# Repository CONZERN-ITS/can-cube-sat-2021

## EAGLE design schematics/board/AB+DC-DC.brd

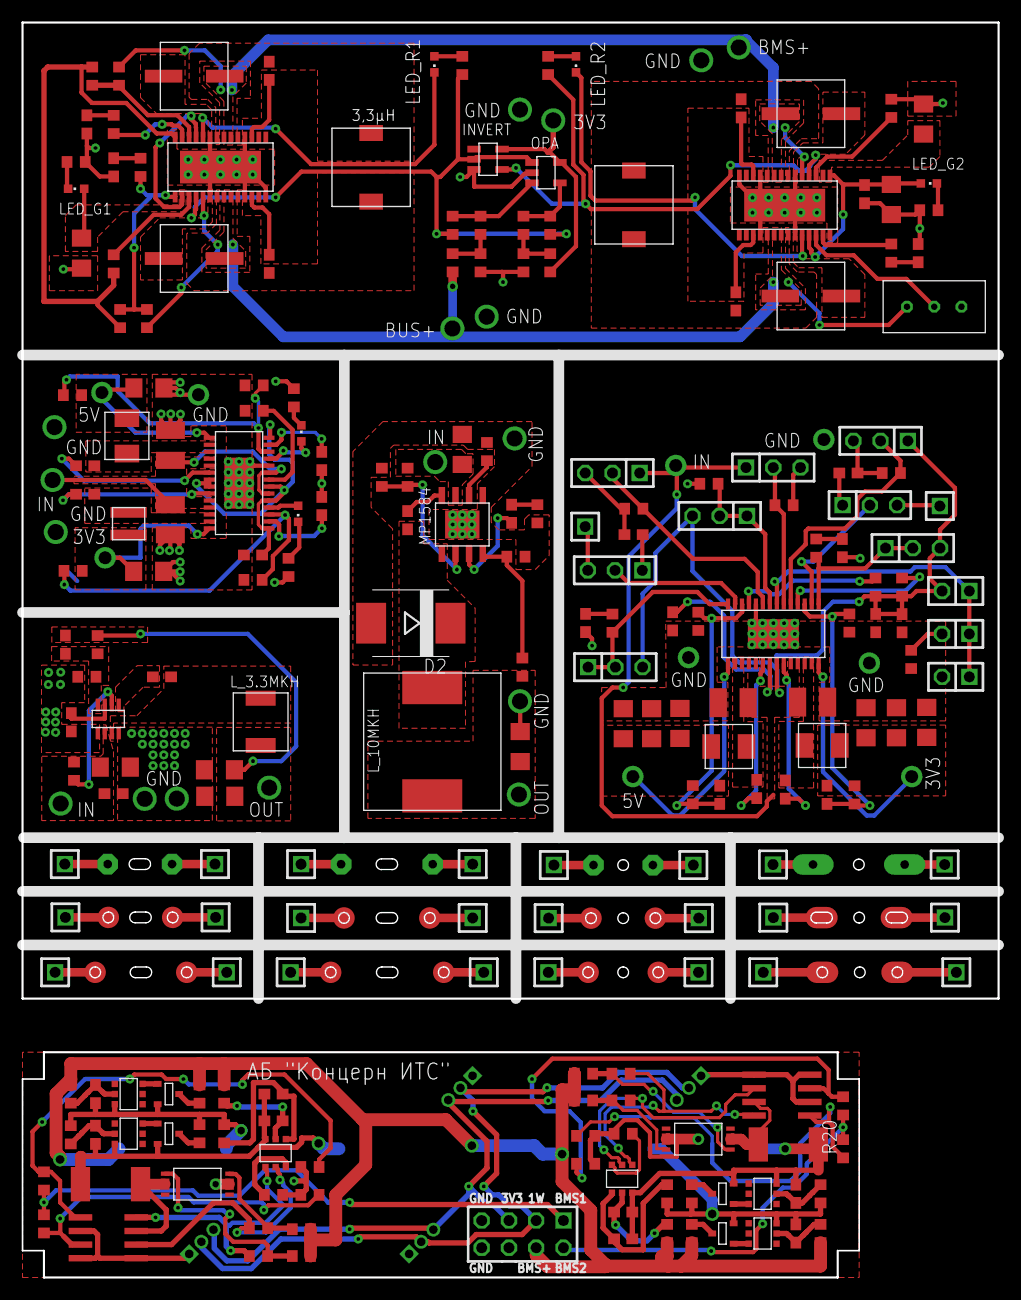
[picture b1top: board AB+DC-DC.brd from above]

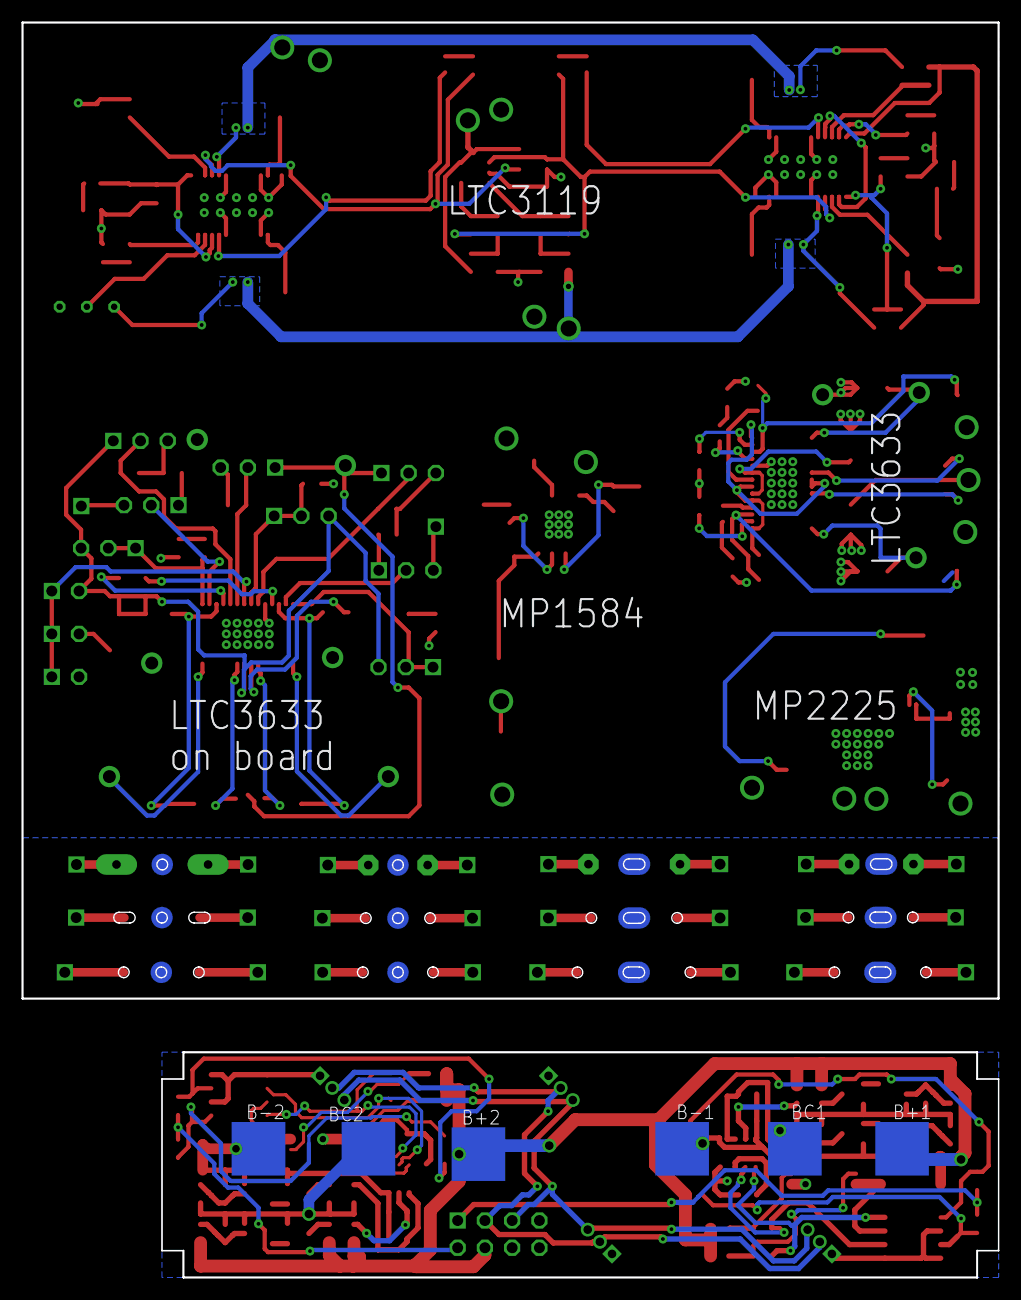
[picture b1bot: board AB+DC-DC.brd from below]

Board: 2 copper layers, 91.0 x 117.0 mm, 242 parts (6 on the bottom side), 164 nets.

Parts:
3,3µH: 3,3µ; B82472G6
3,3µH1: 3,3µH; B82472G6
AB1: 2X04
B+1, B+2: BATTERY
B-1, B-2: BATTERY
BC1, BC2: BATTERY
C1, C2, C3, C4, C5, C6, C8, C11, C12, C18, C25, C26, C27, C28, C33, C34, C48, C49, C55, C56, C61: 0,1µ; C0603
C7, C9, C13, C15, C20, C21, C38, C39, C40, C41: 22µ; C1206
C10, C42, C43, C62: 10µ; C1206
C14: 2,2µ; C0603
C16, C17, C46, C47: 47µ; C1210
C19: 33p; C0603
C22, C23, C36: 220p; C0603
C24, C30, C31: 1µ; C0603
C29, C32, C44, C45: 4.7nF; C0603
C35, C37: 10p; C0603
C50, C57: 680p; C0603
C51, C58: 4.7µ; C1206
C52: 3,3n; C0603
C53, C59: 150µ; ECAP150
C54, C60: 220µ; ECAP220
D2: SMC
DS18B20, DS18B20A, DS18B20B, DS18B20C: CONNECT1X3
INVERT: INVERTER; SOT23-5
JP1, JP2, JP3: 1X02
JP4, JP5, JP6, JP7, JP8, JP9, JP10, JP11: 1X03
JP12, JP13, JP14, JP15, JP16, JP17, JP18, JP19, JP20, JP21, JP22, JP23, JP24, JP25, JP26, JP27, JP28, JP29, JP30, JP31, JP32, JP33, JP34, JP35, JP36, JP37: 1X01
LED1, LED2: CHIPLED_0603
LED_G1, LED_G2: CHIPLED_0603
LED_R1, LED_R2: CHIPLED_0603
OPA: OPA333; SOT23-5
R1, R26, R31, R49, R60, R61, R62, R100: 2k; R0603
R2, R3, R50, R51: 330R; R0603
R4, R5, R6, R7, R9, R10, R15, R16, R52, R53, R54, R55: 100R; R0603
R8, R56: R05; R2512
R11, R12, R17, R18, R30, R34, R42, R43: 100k; R0603
R13, R14, R19, R20: 2k26; R0603
R21: 73,2k; R0603
R22: 45,3k; R0603
R23, R24, R37, R66, R74, R76: 10k; R0603
R25: 162k; R0603
R27, R94, R95, R98, R99: 200k; R0603
R28, R36: 40k2; R0603
R29: 124k; R0603
R32: 24k9; R0603
R33: 68k1; R0603
R35: 8k87; R0603
R38, R40: 13k; R0603
R39: 324k; R0603
R41, R44, R45, R65: 1M; R0603
R46: 11k5; R0603
R47: 18k7; R0603
R48, R57: 84k5; R0603
R58, R59, R67, R68, R69, R75, R77: 150k; R0603
R63: 910k; R0603
R64: 330k; R0603
R70: 24k3; R0603
R71, R73: 51k; R0603
R72: 232k; R0603
U$1, U$26: FS8205A-
U$2, U$10: MOCD217M; SOIC8
U$3, U$45: HY2120; SOT23-6
U$4, U$5, U$46, U$47: HY2213"; SOT23-6
U$6, U$7, U$48, U$49: SI2302CDS; SOT23-3
U$8, U$16: LTC3633+VIA
U$9: MP1584+VIA
U$11: 1µH; VLS3012HBX
U$12: SPM4020
U$13: L_10MKH; L_12X12
U$14: MP2225; TSOT23-8
U$15: L_3.3MKH; L_SPM5020
U$17, U$18: L_2.2MKH; L_SPM4020
U$19: GRAFITGRAFIT1; GRAFIT1
U$20: GRAFITGRAFIT1_1; GRAFIT1_1
U$21: GRAFITGRAFIT1_2; GRAFIT1_2
U$22: GRAFITGRAFIT2; GRAFIT2
U$23: GRAFITGRAFIT2_1; GRAFIT2_1
U$24: GRAFITGRAFIT2_2; GRAFIT2_2
U$25: GRAFITGRAFIT3; GRAFIT3
U$27: GRAFITGRAFIT3_1; GRAFIT3_1
U$28: GRAFITGRAFIT3_2; GRAFIT3_2
U$29: GRAFITGRAFIT4; GRAFIT4
U$30: GRAFITGRAFIT4_1; GRAFIT4_1
U$31: GRAFITGRAFIT4_2; GRAFIT4_2
U$32, U$59: LTC31191; LTC3119+VIA
U$33: 32961; 3296W

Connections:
1.65: R71.2, R73.1, R74.2
1W: AB1.3, DS18B20.2, DS18B20A.2, DS18B20B.2, DS18B20C.2
3.3: INVERT.P$5, OPA.P$5, R73.2
3V1: C9.1, R29.1, U$13.P$1
3V3: AB1.5, DS18B20.3, DS18B20A.3, DS18B20B.3, DS18B20C.3
5V: C15.1, R21.2, U$8.15, U$12.P$2
90: R65.1, R66.2, R67.2, U$59.15
A: INVERT.P$2, OPA.P$1, R61.1, R75.2, R77.2, U$59.18
B-1: B-1.P$1, C1.2, C2.2, C4.2, R8.2, U$3.6, U$5.3, U$7.2
B-2: B-2.P$1, C25.2, C26.2, C28.2, R56.2, U$45.6, U$47.3, U$49.2
BC1: BC1.P$1, C3.2, R3.2, R5.2, R7.2, U$4.3, U$6.2
BC2: BC2.P$1, C27.2, R51.2, R53.2, R55.2, U$46.3, U$48.2
BMS1: AB1.1, R13.2, R14.2
BMS2: AB1.2, R19.2, R20.2
BMS+: AB1.4, B+1.P$1, B+2.P$1, R2.2, R4.2, R6.2, R11.1, R12.2, R17.1, R18.2, R50.2, R52.2, R54.2
BUS+: C16.1, C17.1, U$8.6, U$8.9, U$8.18, U$8.19, U$8.24, U$8.25
FB1: C37.1, R47.1, R57.2, U$16.3
FB2: C35.1, R46.1, R48.2, U$16.12
GND: AB1.7, AB1.8, DS18B20.1, DS18B20A.1, DS18B20B.1, DS18B20C.1, R1.1, R49.1, R94.1, R95.1, R98.1, R99.1, U$1.23, U$2.2, U$2.4, U$2.5, U$10.2, U$10.4, U$10.5, U$26.23
GND1: C7.2, C9.2, C10.1, C12.1, C13.1, C14.1, C15.2, C16.2, C17.2, C18.1, C20.1, C21.1, C22.1, C23.1, C24.1, C29.1, C30.1, C31.1, C32.1, C38.1, C39.1, C40.1, C41.1, C42.1, C43.1, C44.1, C45.1, C46.1, C47.1, C50.2, C51.2, C52.2, C53.P$2, C54.P$2, C57.2, C58.2, C59.P$2, C60.P$2, C61.2, C62.2, D2.A, INVERT.P$3, JP3.2, JP7.3, JP9.3, JP10.3, OPA.P$2, R23.2, R24.2, R25.2, R26.1, R27.1, R28.2, R31.1, R32.2, R33.2, R35.2, R37.2, R39.2, R41.2, R44.2, R45.2, R46.2, R47.2, R58.1, R60.1, R64.2, R67.1, R68.1, R70.2, R71.1, R100.1, U$8.10, U$8.HEAT, U$8.P$1, U$8.P$2, U$8.P$3, U$8.P$4, U$8.P$5, U$8.P$6, U$8.P$7, U$8.P$8, U$8.P$9, U$8.P$10, U$8.P$11, U$8.P$12, U$8.P$13, U$8.P$14, U$8.P$15, U$9.P$5, U$9.P$9, U$9.P$10, U$9.P$11, U$9.P$12, U$9.P$13, U$9.P$14, U$9.P$15, U$9.P$16, U$9.P$17, U$9.P$18, U$14.P$1, U$14.P$4, U$16.10, U$16.HEAT, U$16.P$1, U$16.P$2, U$16.P$3, U$16.P$4, U$16.P$5, U$16.P$6, U$16.P$7, U$16.P$8, U$16.P$9, U$16.P$10, U$16.P$11, U$16.P$12, U$16.P$13, U$16.P$14, U$16.P$15, U$32.4, U$32.9, U$32.14, U$32.20, U$32.25, U$32.28, U$32.29, U$32.P$1, U$32.P$2, U$32.P$3, U$32.P$4, U$32.P$5, U$32.P$6, U$32.P$7, U$32.P$8, U$32.P$9, U$32.P$10, U$33.P$1, U$59.4, U$59.9, U$59.14, U$59.20, U$59.25, U$59.28, U$59.29, U$59.P$1, U$59.P$2, U$59.P$3, U$59.P$4, U$59.P$5, U$59.P$6, U$59.P$7, U$59.P$8, U$59.P$9, U$59.P$10
INA_BMS+: C53.P$1, C60.P$1, R72.2, U$32.19, U$32.22, U$32.23, U$59.6, U$59.7
INA_BUS+: C54.P$1, C59.P$1, R63.1, R65.2, U$32.6, U$32.7, U$33.P$3, U$59.19, U$59.22, U$59.23
INTVCC: C30.2, C31.2, JP1.2, JP4.3, JP5.3, JP6.3, JP10.1, R42.2, R43.2, U$16.22
unnamed: R10.1, R11.2, U$26.5
unnamed: R9.1, R12.1, U$26.4
unnamed: R20.1, R98.2, U$10.1
unnamed: C1.1, R2.1, U$3.5
unnamed: R49.2, U$45.3
unnamed: C3.1, R6.1, U$4.2
unnamed: U$4.6, U$6.1
unnamed: C4.1, R7.1, U$5.2
unnamed: U$5.6, U$7.1
unnamed: R16.1, R17.2, U$1.5
unnamed: R4.1, U$6.3
unnamed: R5.1, U$7.3
unnamed: R1.2, U$3.3
unnamed: R15.1, R18.1, U$1.4
unnamed: C2.1, R3.1, U$3.4
unnamed: R25.1, U$8.8
unnamed: R14.1, R94.2, U$2.1
unnamed: R13.1, R95.2, U$2.3
unnamed: R19.1, R99.2, U$10.3
unnamed: LED1.C, R31.2
unnamed: LED2.C, R26.2
unnamed: LED2.A, U$8.11
unnamed: C8.2, U$9.P$8
unnamed: C14.2, U$8.1, U$8.5, U$8.7, U$8.14, U$8.21, U$8.22
unnamed: R22.1, R23.1, U$8.3
unnamed: C8.1, D2.C, U$9.P$1, U$13.P$2
unnamed: R27.2, U$9.P$6
unnamed: C6.1, U$8.26, U$8.27, U$11.P$1
unnamed: R28.1, R29.2, U$9.P$4
unnamed: R30.1, R32.1, U$9.P$2
unnamed: C6.2, U$8.23
unnamed: C5.1, U$8.20
unnamed: C5.2, U$8.16, U$8.17, U$12.P$1
unnamed: C10.2, R30.2, U$9.P$7
unnamed: C36.1, R33.1
unnamed: C36.2, U$9.P$3
unnamed: C11.2, U$14.P$5
unnamed: C11.1, U$14.P$3, U$15.P$2
unnamed: R21.1, R24.1, U$8.12
unnamed: C12.2, U$14.P$7
unnamed: R34.2, U$14.P$6
unnamed: C13.2, C18.2, R34.1, U$14.P$2
unnamed: C19.2, R35.1, R36.1, U$14.P$8
unnamed: C19.1, C20.2, C21.2, R36.2, U$15.P$1
unnamed: JP1.1, JP2.1, JP3.1, U$16.7
unnamed: JP2.2, R37.1
unnamed: LED1.A, U$8.4
unnamed: JP4.1, JP4.2, R38.2, U$16.14
unnamed: C22.2, R38.1
unnamed: JP5.1, JP5.2, R39.1, U$16.8
unnamed: JP6.1, JP6.2, R40.2, U$16.1
unnamed: C23.2, R40.1
unnamed: C24.2, U$16.21
unnamed: C33.1, U$16.16, U$16.17, U$17.P$2
unnamed: C34.1, U$16.26, U$16.27, U$18.P$2
unnamed: JP7.2, R41.1, U$16.9
unnamed: R42.1, U$16.11
unnamed: JP8.2, U$16.13
unnamed: R43.1, U$16.4
unnamed: JP9.2, R44.1, U$16.6
unnamed: C29.2, JP8.1
unnamed: JP10.2, R45.1, U$16.5
unnamed: JP11.2, U$16.2
unnamed: C32.2, JP11.1
unnamed: C33.2, U$16.20
unnamed: C34.2, U$16.23
unnamed: JP8.3, JP13.1
unnamed: JP11.3, JP12.1
unnamed: C44.2, U$8.2
unnamed: C45.2, U$8.13
unnamed: R52.1, U$48.3
unnamed: JP14.1, U$22.P$1
unnamed: JP15.1, U$23.P$1
unnamed: JP16.1, U$24.P$1
unnamed: JP17.1, U$22.P$2
unnamed: JP18.1, U$23.P$2
unnamed: JP19.1, U$24.P$2
unnamed: JP20.1, U$25.P$1
unnamed: JP21.1, U$27.P$1
unnamed: JP22.1, U$28.P$1
unnamed: JP23.1, U$25.P$2
unnamed: JP24.1, U$27.P$2
unnamed: JP25.1, U$28.P$2
unnamed: JP26.1, U$29.P$1
unnamed: R53.1, U$49.3
unnamed: JP27.1, U$30.P$1
unnamed: JP28.1, U$31.P$1
unnamed: JP29.1, U$29.P$2
unnamed: JP30.1, U$30.P$2
unnamed: JP31.1, U$31.P$2
unnamed: JP32.1, U$19.P$1
unnamed: JP33.1, U$20.P$1
unnamed: JP34.1, U$21.P$1
unnamed: JP35.1, U$19.P$2
unnamed: JP36.1, U$20.P$2
unnamed: JP37.1, U$21.P$2
unnamed: C25.1, R50.1, U$45.5
unnamed: R70.1, R72.1, U$59.12
unnamed: C27.1, R54.1, U$46.2
unnamed: U$46.6, U$48.1
unnamed: 3,3µH1.2, C55.1, U$32.21, U$32.24
unnamed: U$47.6, U$49.1
unnamed: 3,3µH1.1, C56.1, U$32.5, U$32.8
unnamed: R58.2, U$32.17
unnamed: C55.2, U$32.26
unnamed: R59.1, U$32.13
unnamed: C26.1, R51.1, U$45.4
unnamed: C28.1, R55.1, U$47.2
unnamed: C56.2, U$32.3
unnamed: U$32.12, U$33.P$2
unnamed: C57.1, R59.2
unnamed: LED_G1.C, R100.2
unnamed: LED_G2.C, R60.2
unnamed: OPA.P$3, R76.1, R77.1
unnamed: LED_R1.A, R61.2
unnamed: LED_R2.A, R62.2
unnamed: C49.2, U$59.3
unnamed: 3,3µH.2, C48.1, U$59.21, U$59.24
unnamed: 3,3µH.1, C49.1, U$59.5, U$59.8
unnamed: R69.1, U$59.13
unnamed: C50.1, R69.2
unnamed: C52.1, R66.1
unnamed: R68.2, U$59.17
unnamed: C48.2, U$59.26
unnamed: C58.1, C61.1, C62.1, LED_G2.A, U$32.11, U$32.15, U$32.16
unnamed: C51.1, LED_G1.A, U$59.11, U$59.16
unnamed: OPA.P$4, R74.1, R75.1
NO_GND1: R8.1, U$2.7, U$26.67
NO_GND2: R56.1, U$1.67, U$10.7
OC1: R9.2, U$2.6, U$3.2
OC2: R15.2, U$10.6, U$45.2
OD1: R10.2, U$2.8, U$3.1
OD2: R16.2, U$10.8, U$45.1
PGOOD1: LED_R1.C, U$59.10
PGOOD2: LED_R2.C, U$32.10
RUN: R63.2, R64.1, R76.2
VDD: C7.1, R22.2, U$8.28, U$11.P$2
VIN: C46.2, C47.2, JP7.1, JP9.1, U$16.18, U$16.19, U$16.24, U$16.25
VON1: C37.2, C40.2, C41.2, C43.2, R57.1, U$16.28, U$18.P$1
VON2: C35.2, C38.2, C39.2, C42.2, R48.1, U$16.15, U$17.P$1
Y: INVERT.P$4, R62.1, U$32.18

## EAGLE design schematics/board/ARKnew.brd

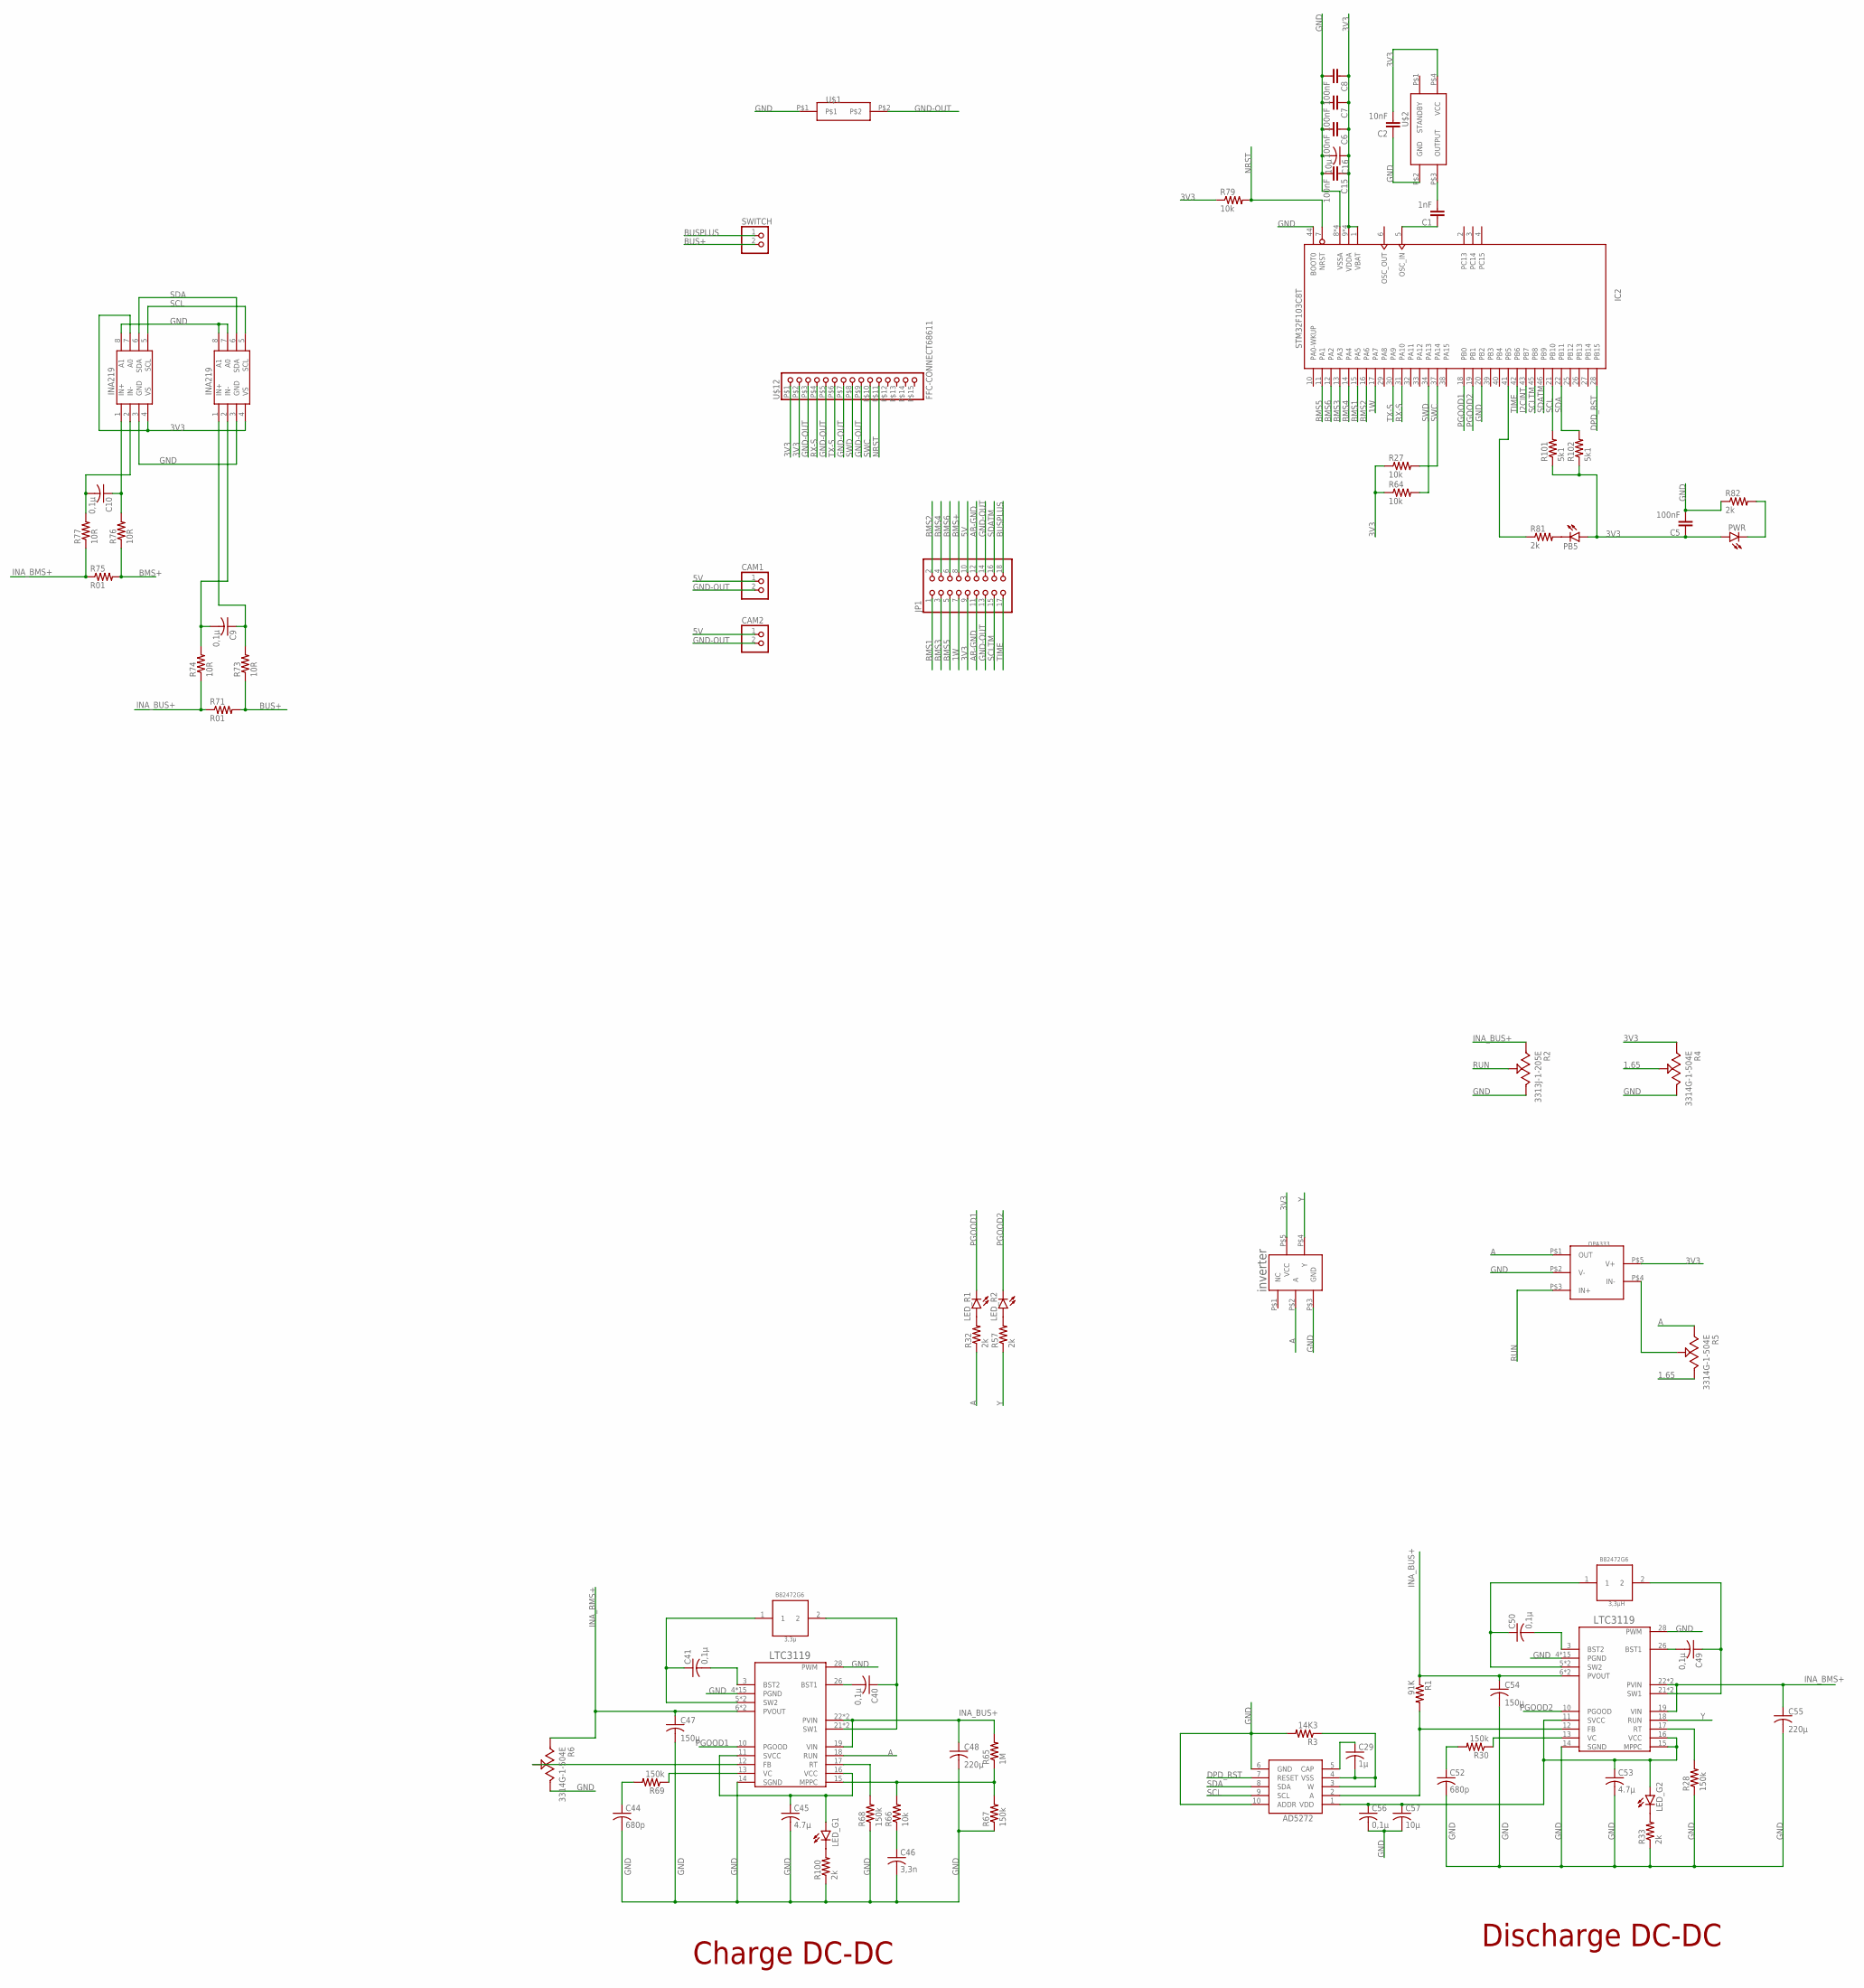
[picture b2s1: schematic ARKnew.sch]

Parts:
3,3µH: 3,3µ; B82472G6
3,3µH1: 3,3µH; B82472G6
AD5272#2: AD5272; MSOP10
C1: 1nF; C0603
C2: 10nF; C0603
C5, C6, C7, C8, C15: 100nF; C0603
C9, C10, C40, C41, C49, C50, C56: 0,1µ; C0603
C16, C57: 10µ; C1206
C29: 1µ; C0603
C44, C52: 680p; C0603
C45, C53: 4.7µ; C1206
C46: 3,3n; C0603
C47, C54: 150µ; ECAP150-CMD
C48, C55: 220µ; ECAP220-CMD
CAM1, CAM2: PINHD-1X2; 1X02
IC2: STM32F103C8T; LQFP48
INA219#1: INA219AID; SOT23-8
INVERT: INVERTER.; SC70
JP1: PINHD-2X9; 2X09
LED_G1, LED_G2: LEDCHIPLED_0603; CHIPLED_0603
LED_R1, LED_R2: LEDCHIPLED_0603; CHIPLED_0603
OPA: OPA333; SOT23-5
PB5: LEDCHIPLED_0603; CHIPLED_0603
PWR: LEDCHIPLED_0603; CHIPLED_0603
R1: 91K; R0603
R2: 3313J-1-205E; TRIM_3313J-1-205E
R3: 14K3; R0603
R4, R5, R6: 3314G-1-504E; TRIM_3314G-1-504E
R27, R64, R66, R79: 10k; R0603
R28, R30, R67, R68, R69: 150k; R0603
R32, R33, R57, R81, R82, R100: 2k; R0603
R65: 1M; R0603
R71, R75: R01; R2512
R73, R74, R76, R77: 10R; R0603
R101, R102: 5k1; R0603
SWITCH: PINHD-1X2; 1X02
U$1: MF-R400
U$2: Q24
U$12: FFC-CONNECT68611; 68611
U$23, U$59: LTC31191; LTC3119+VIA
U$57: INA219AID; SOT23-8

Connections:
1.65: R4.2 (WIPER), R5.3 (CW)
1W: IC2.17 (PA7), JP1.7
3V3: C2.2, C5.1, C6.1, C7.1, C8.1, C15.1, C16.1, IC2.1 (VBAT), IC2.9 (VDDA), IC2.24 (VDDA), IC2.36 (VDDA), IC2.48 (VDDA), INA219#1.4 (VS), INVERT.P$5 (VCC), JP1.9, OPA.P$5 (V+), PB5.A, PWR.A, R4.1 (CCW), R27.1, R64.1, R79.1, R101.1, R102.1, U$2.P$4 (VCC), U$12.P$1 (1), U$12.P$2 (2), U$57.4 (VS), U$57.7 (A0)
5V: CAM1.1, CAM2.1, JP1.10
90: R65.1, R66.2, R67.2, U$59.15 (MPPC)
302: OPA.P$4 (IN-), R5.2 (WIPER)
A: INVERT.P$2 (A), OPA.P$1 (OUT), R5.1 (CCW), R32.1, U$59.18 (RUN)
AB-GND: JP1.11, JP1.12
BMS1: IC2.15 (PA5), JP1.1
BMS2: IC2.16 (PA6), JP1.2
BMS3: IC2.13 (PA3), JP1.3
BMS4: IC2.14 (PA4), JP1.4
BMS5: IC2.11 (PA1), JP1.5
BMS6: IC2.12 (PA2), JP1.6
BMS+: JP1.8, R75.2, R76.1
BUS+: R71.2, R73.1, SWITCH.2
BUSPLUS: JP1.18, SWITCH.1
DPD_RST: AD5272#2.7 (RESET), IC2.28 (PB15)
GND: AD5272#2.6 (GND), AD5272#2.10 (ADDR), C2.1, C5.2, C6.2, C7.2, C8.2, C15.2, C16.2, C44.2, C45.2, C46.2, C47.P$2 (2), C48.P$2 (2), C52.2, C53.2, C54.P$2 (2), C55.P$2 (2), C56.2, C57.2, IC2.8 (VSSA), IC2.20 (PB2), IC2.23 (VSSA), IC2.35 (VSSA), IC2.44 (BOOT0), IC2.47 (VSSA), INA219#1.3 (GND), INA219#1.7 (A0), INA219#1.8 (A1), INVERT.P$3 (GND), OPA.P$2 (V-), R2.3 (CW), R3.2, R4.3 (CW), R6.3 (CW), R28.1, R33.1, R67.1, R68.1, R82.1, R100.1, U$1.P$1, U$2.P$2 (GND), U$23.4 (PGND), U$23.9 (PGND), U$23.14 (SGND), U$23.20 (PGND), U$23.25 (PGND), U$23.28 (PWM), U$23.29 (PGND), U$23.P$1 (PGND), U$23.P$2 (PGND), U$23.P$3 (PGND), U$23.P$4 (PGND), U$23.P$5 (PGND), U$23.P$6 (PGND), U$23.P$7 (PGND), U$23.P$8 (PGND), U$23.P$9 (PGND), U$23.P$10 (PGND), U$57.3 (GND), U$57.8 (A1), U$59.4 (PGND), U$59.9 (PGND), U$59.14 (SGND), U$59.20 (PGND), U$59.25 (PGND), U$59.28 (PWM), U$59.29 (PGND), U$59.P$1 (PGND), U$59.P$2 (PGND), U$59.P$3 (PGND), U$59.P$4 (PGND), U$59.P$5 (PGND), U$59.P$6 (PGND), U$59.P$7 (PGND), U$59.P$8 (PGND), U$59.P$9 (PGND), U$59.P$10 (PGND)
GND-OUT: CAM1.2, CAM2.2, JP1.13, JP1.14, U$1.P$2, U$12.P$3 (3), U$12.P$5 (5), U$12.P$7 (7), U$12.P$9 (9)
I2CINT: IC2.43 (PB7)
INA_BMS+: C47.P$1 (1), C55.P$1 (1), R6.1 (CCW), R75.1, R77.1, U$23.19 (VIN), U$23.22 (PVIN), U$23.23 (PVIN), U$59.6 (PVOUT), U$59.7 (PVOUT)
INA_BUS+: C48.P$1 (1), C54.P$1 (1), R1.1, R2.1 (CCW), R65.2, R71.1, R74.1, U$23.6 (PVOUT), U$23.7 (PVOUT), U$59.19 (VIN), U$59.22 (PVIN), U$59.23 (PVIN)
unnamed: C1.1, IC2.5 (OSC_IN)
unnamed: AD5272#2.2 (A), R1.2, U$23.12 (FB)
unnamed: C1.2, U$2.P$3 (OUTPUT)
unnamed: C9.2, INA219#1.2 (IN-), R74.2
unnamed: PB5.C, R81.2
unnamed: AD5272#2.3 (W), AD5272#2.4 (VSS), C29.2, R3.1
unnamed: AD5272#2.5 (CAP), C29.1
unnamed: 3,3µH1.2, C49.1, U$23.21 (SW1), U$23.24 (SW1)
unnamed: 3,3µH1.1, C50.1, U$23.5 (SW2), U$23.8 (SW2)
unnamed: R28.2, U$23.17 (RT)
unnamed: C49.2, U$23.26 (BST1)
unnamed: R30.1, U$23.13 (VC)
unnamed: C52.1, R30.2
unnamed: C50.2, U$23.3 (BST2)
unnamed: LED_R1.A, R32.2
unnamed: LED_R2.A, R57.2
unnamed: R6.2 (WIPER), U$59.12 (FB)
unnamed: LED_G1.C, R100.2
unnamed: LED_G2.C, R33.2
unnamed: C41.2, U$59.3 (BST2)
unnamed: 3,3µH.2, C40.1, U$59.21 (SW1), U$59.24 (SW1)
unnamed: 3,3µH.1, C41.1, U$59.5 (SW2), U$59.8 (SW2)
unnamed: R69.1, U$59.13 (VC)
unnamed: C44.1, R69.2
unnamed: C46.1, R66.1
unnamed: R68.2, U$59.17 (RT)
unnamed: C40.2, U$59.26 (BST1)
unnamed: C9.1, INA219#1.1 (IN+), R73.2
unnamed: C10.1, R76.2, U$57.1 (IN+)
unnamed: C10.2, R77.2, U$57.2 (IN-)
unnamed: PWR.C, R82.2
unnamed: IC2.41 (PB5), R81.1
unnamed: AD5272#2.1 (VDD), C53.1, C56.1, C57.1, LED_G2.A, U$23.11 (SVCC), U$23.15 (MPPC), U$23.16 (VCC)
unnamed: C45.1, LED_G1.A, U$59.11 (SVCC), U$59.16 (VCC)
NRST: IC2.7 (NRST), R79.2, U$12.P$11 (11)
PGOOD1: IC2.18 (PB0), LED_R1.C, U$59.10 (PGOOD)
PGOOD2: IC2.19 (PB1), LED_R2.C, U$23.10 (PGOOD)
RUN: OPA.P$3 (IN+), R2.2 (WIPER)
RX-S: IC2.31 (PA10), U$12.P$4 (4)
SCL: AD5272#2.9 (SCL), IC2.21 (PB10), INA219#1.5 (SCL), R101.2, U$57.5 (SCL)
SCLTM: IC2.45 (PB8), JP1.15
SDA: AD5272#2.8 (SDA), IC2.22 (PB11), INA219#1.6 (SDA), R102.2, U$57.6 (SDA)
SDATM: IC2.46 (PB9), JP1.16
SWC: IC2.37 (PA14), R27.2, U$12.P$10 (10)
SWD: IC2.34 (PA13), R64.2, U$12.P$8 (8)
TIME: IC2.42 (PB6), JP1.17
TX-S: IC2.30 (PA9), U$12.P$6 (6)
Y: INVERT.P$4 (Y), R57.1, U$23.18 (RUN)

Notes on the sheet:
Charge DC-DC
Discharge DC-DC

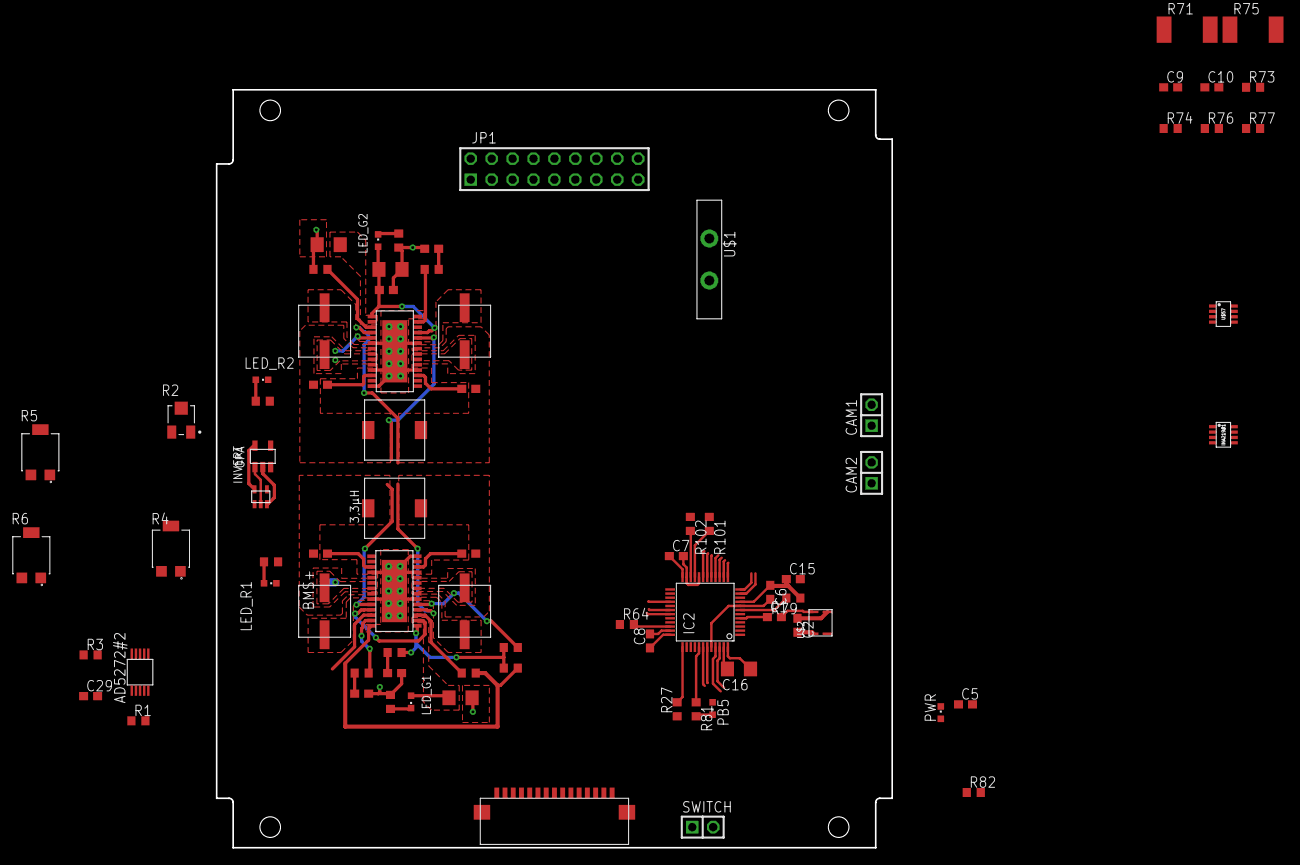
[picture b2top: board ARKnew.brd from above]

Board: 2 copper layers, 82.0 x 92.0 mm, 79 parts (0 on the bottom side), 70 nets.
